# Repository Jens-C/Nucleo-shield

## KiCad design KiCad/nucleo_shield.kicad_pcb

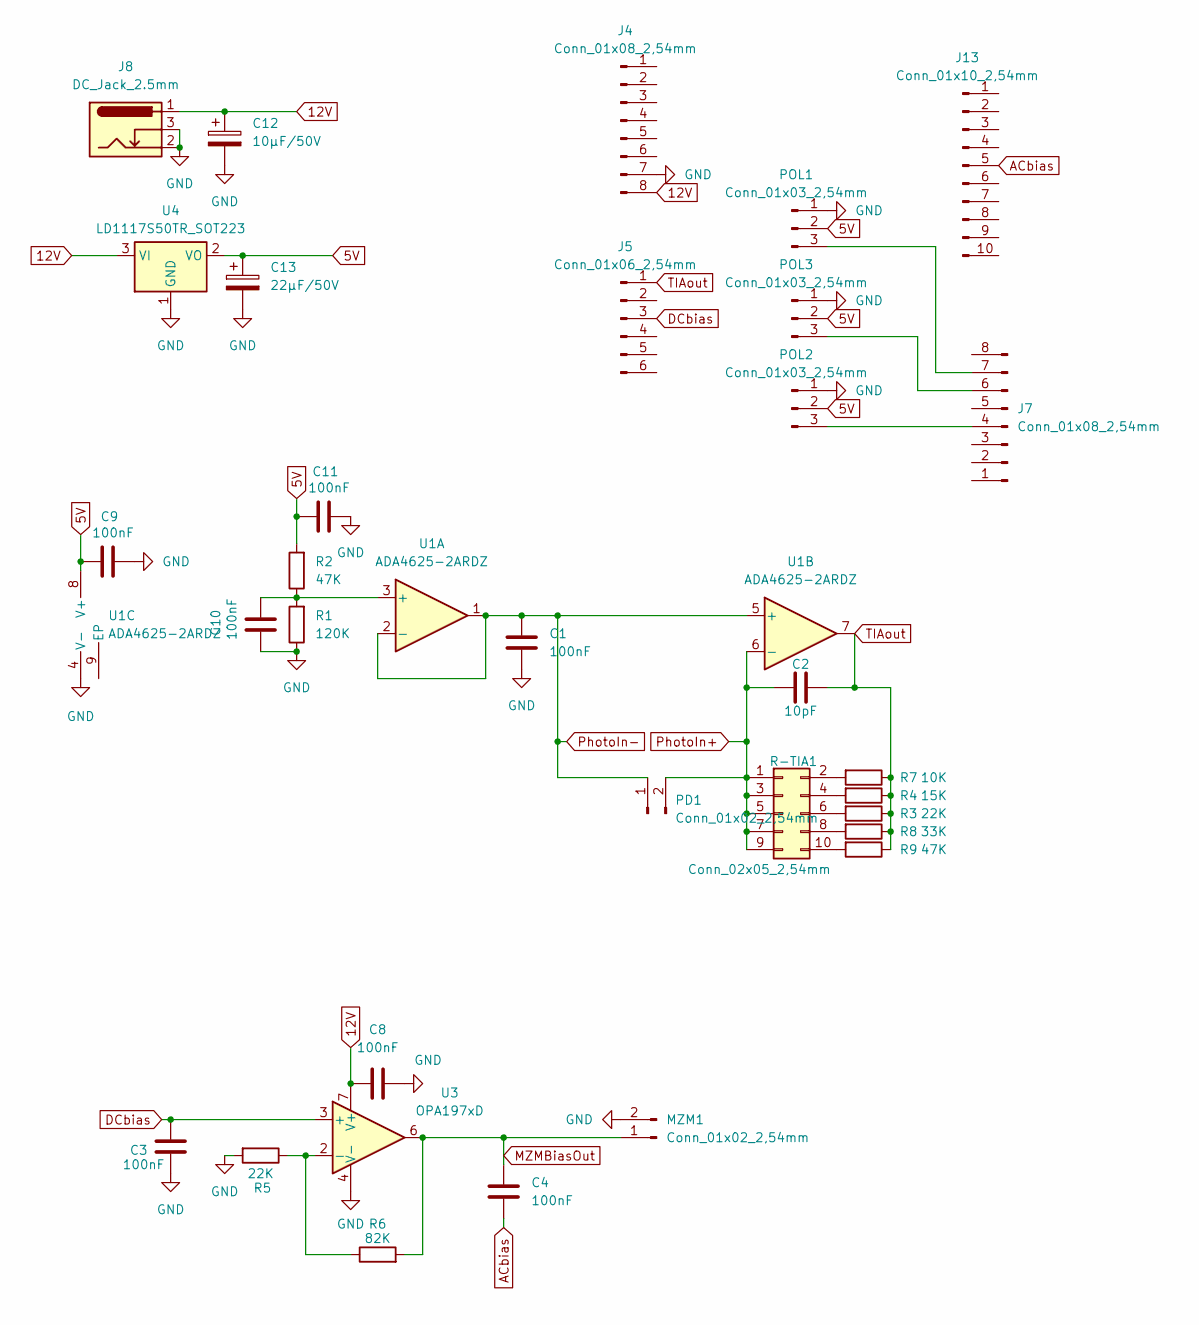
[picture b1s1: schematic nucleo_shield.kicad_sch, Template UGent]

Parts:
C1, C3, C4, C8, C9, C10, C11: 100nF_0603; C_0603_1608Metric
C2: 10pF_0603; C_0603_1608Metric
C12: 10µF/50V; CP_Radial_D5.0mm_P2.00mm
C13: 22µF/50V; CP_Radial_D5.0mm_P2.00mm
J4, J7: Conn_01x08_2,54mm; PinHeader_1x08_P2.54mm_Vertical
J5: Conn_01x06_2,54mm; PinHeader_1x06_P2.54mm_Vertical
J8: DC_Jack_2.5mm; BarrelJack_CUI_PJ-102AH_Horizontal
J13: Conn_01x10_2,54mm; PinHeader_1x10_P2.54mm_Vertical
MZM1: Conn_01x02_2,54mm; PinHeader_1x02_P2.54mm_Vertical
PD1: Conn_01x02_2,54mm; PinHeader_1x02_P2.54mm_Vertical
POL1, POL2, POL3: Conn_01x03_2,54mm; PinHeader_1x03_P2.54mm_Vertical
R1: 120K; R_0603_1608Metric
R2, R9: 47K; R_0603_1608Metric
R3, R5: 22K; R_0603_1608Metric
R4: 15K; R_0603_1608Metric
R6: 82K; R_0603_1608Metric
R7: 10K; R_0603_1608Metric
R8: 33K; R_0603_1608Metric
R-TIA1: Conn_02x05_2,54mm; PinHeader_2x05_P2.54mm_Vertical
U1: ADA4625-2ARDZ; SOIC-8-1EP_3.9x4.9mm_P1.27mm_EP2.29x3mm
U3: OPA197xD; SOIC-8_3.9x4.9mm_P1.27mm
U4: LD1117S50TR_SOT223; SOT-223-3_TabPin2

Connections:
5V: C9.1, C11.1, C13.1, POL1.2, POL2.2, POL3.2, R2.2, U1.8 (V+), U4.2 (VO)
12V: C8.1, C12.1, J4.8, J8.1, U3.7 (V+), U4.3 (VI)
ACbias: C4.2, J13.5
DCbias: C3.1, J5.3, U3.3 (+)
GND: C1.2, C3.2, C8.2, C9.2, C10.1, C11.2, C12.2, C13.2, J4.7, J8.2, J8.3, MZM1.2, POL1.1, POL2.1, POL3.1, R1.1, R5.2, U1.4 (V-), U3.4 (V-), U4.1 (GND)
MZMBiasOut: C4.1, MZM1.1, R6.2, U3.6
unnamed: J7.4, POL2.3
unnamed: J7.6, POL3.3
unnamed: J7.7, POL1.3
unnamed: R7.2, R-TIA1.2
unnamed: R4.2, R-TIA1.4
unnamed: R3.2, R-TIA1.6
unnamed: R8.2, R-TIA1.8
unnamed: R9.2, R-TIA1.10
unnamed: C10.2, R1.2, R2.1, U1.3 (+)
unnamed: R5.1, R6.1, U3.2 (-)
PhotoIn+: C2.2, PD1.2, R-TIA1.1, R-TIA1.3, R-TIA1.5, R-TIA1.7, R-TIA1.9, U1.6 (-)
PhotoIn-: C1.1, PD1.1, U1.1, U1.2 (-), U1.5 (+)
TIAout: C2.1, J5.1, R3.1, R4.1, R7.1, R8.1, R9.1, U1.7

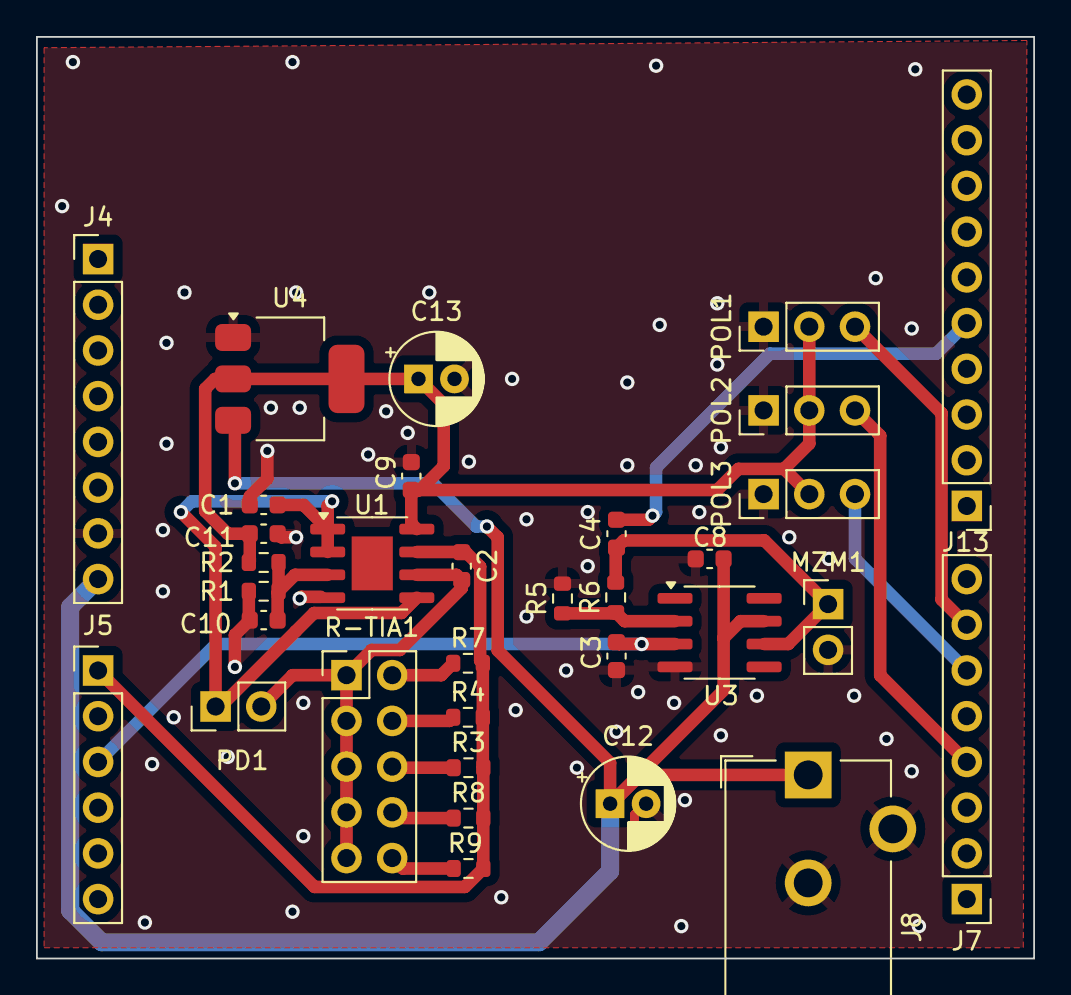
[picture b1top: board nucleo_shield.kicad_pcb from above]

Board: 2 copper layers, 55.4 x 51.2 mm, 33 parts (0 on the bottom side), 19 nets.

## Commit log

2025-02-26 schematic +pcb
2025-02-26 added 12v source for nucleo
